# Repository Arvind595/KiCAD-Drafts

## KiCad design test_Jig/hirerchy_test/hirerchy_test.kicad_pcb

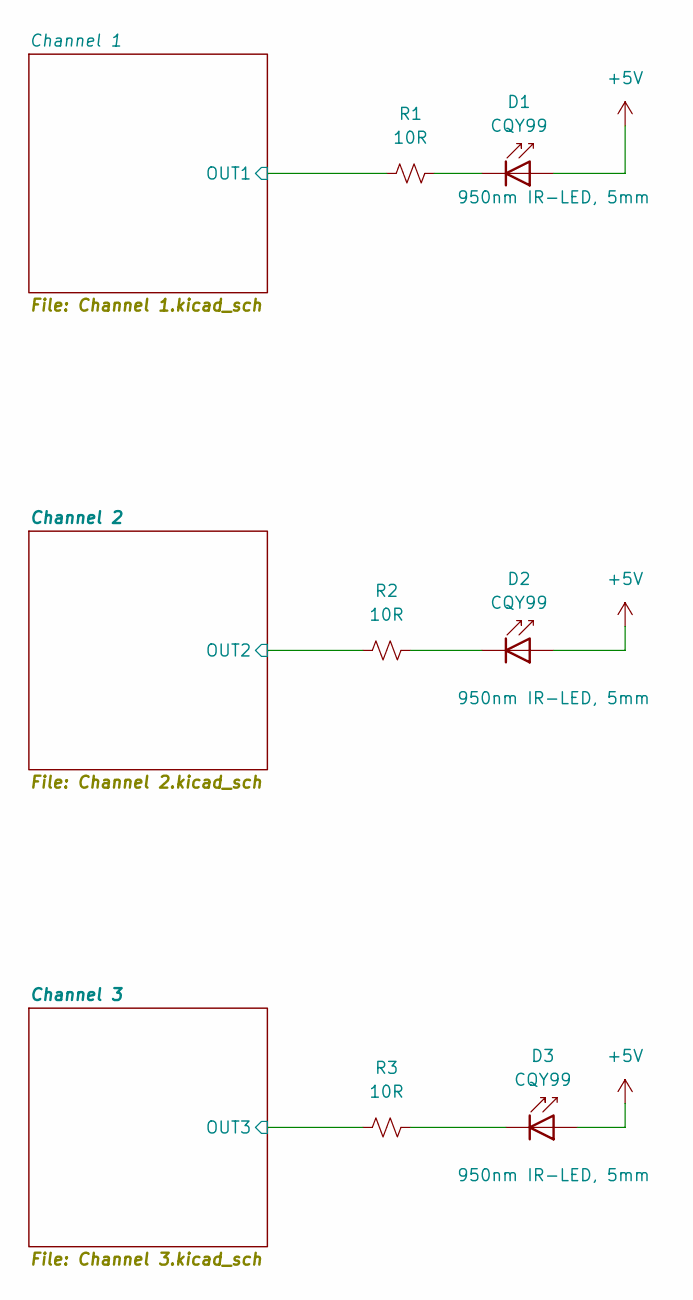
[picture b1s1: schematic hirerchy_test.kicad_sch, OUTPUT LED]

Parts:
D1, D2, D3: CQY99; LED_D5.0mm_IRGrey
R1, R2, R3: 10R; R_0805_2012Metric

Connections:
+5V: D1.2 (A), D2.2 (A), D3.2 (A); also elsewhere on the board
/Channel 1/OUT1: R1.1; also elsewhere on the board
/Channel 2/OUT2: R2.1; also elsewhere on the board
/Channel 3/OUT3: R3.1; also elsewhere on the board
unnamed: D1.1 (K), R1.2
unnamed: D2.1 (K), R2.2
unnamed: D3.1 (K), R3.2

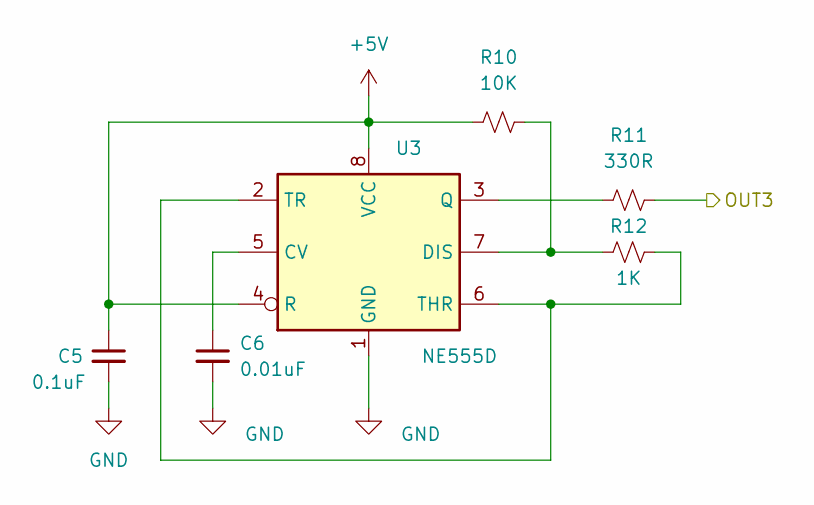
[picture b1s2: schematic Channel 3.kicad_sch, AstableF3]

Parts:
C5: 0.1uF; C_0805_2012Metric
C6: 0.01uF; C_0805_2012Metric
R10: 10K; R_0805_2012Metric
R11: 330R; R_0805_2012Metric
R12: 1K; R_0805_2012Metric
U3: NE555D; SOIC-8_3.9x4.9mm_P1.27mm

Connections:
+5V: C5.1, R10.1, U3.4 (R), U3.8 (VCC); also elsewhere on the board
/Channel 3/OUT3: R11.2; also elsewhere on the board
GND: C5.2, C6.2, U3.1 (GND); also elsewhere on the board
unnamed: C6.1, U3.5 (CV)
unnamed: R10.2, R12.1, U3.7 (DIS)
unnamed: R11.1, U3.3 (Q)
unnamed: R12.2, U3.2 (TR), U3.6 (THR)

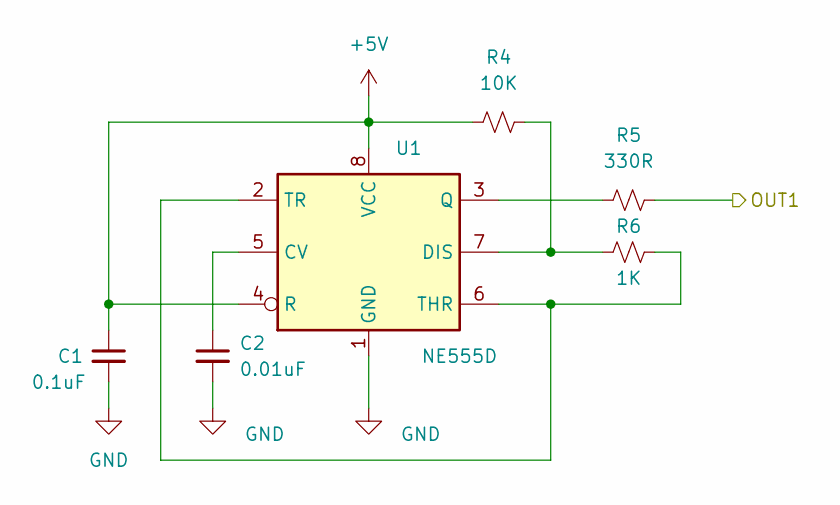
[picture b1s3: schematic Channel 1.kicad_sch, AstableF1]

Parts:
C1: 0.1uF; C_0805_2012Metric
C2: 0.01uF; C_0805_2012Metric
R4: 10K; R_0805_2012Metric
R5: 330R; R_0805_2012Metric
R6: 1K; R_0805_2012Metric
U1: NE555D; SOIC-8_3.9x4.9mm_P1.27mm

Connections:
+5V: C1.1, R4.1, U1.4 (R), U1.8 (VCC); also elsewhere on the board
/Channel 1/OUT1: R5.2; also elsewhere on the board
GND: C1.2, C2.2, U1.1 (GND); also elsewhere on the board
unnamed: C2.1, U1.5 (CV)
unnamed: R4.2, R6.1, U1.7 (DIS)
unnamed: R5.1, U1.3 (Q)
unnamed: R6.2, U1.2 (TR), U1.6 (THR)

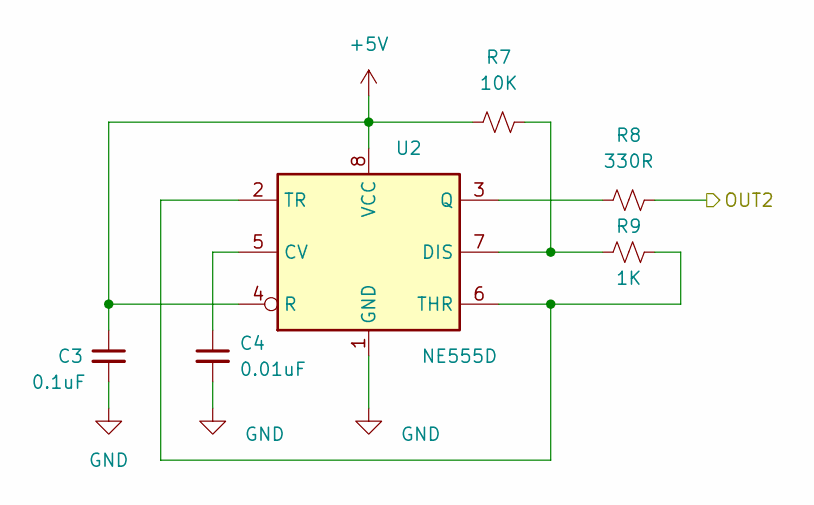
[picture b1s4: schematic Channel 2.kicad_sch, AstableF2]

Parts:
C3: 0.1uF; C_0805_2012Metric
C4: 0.01uF; C_0805_2012Metric
R7: 10K; R_0805_2012Metric
R8: 330R; R_0805_2012Metric
R9: 1K; R_0805_2012Metric
U2: NE555D; SOIC-8_3.9x4.9mm_P1.27mm

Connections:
+5V: C3.1, R7.1, U2.4 (R), U2.8 (VCC); also elsewhere on the board
/Channel 2/OUT2: R8.2; also elsewhere on the board
GND: C3.2, C4.2, U2.1 (GND); also elsewhere on the board
unnamed: C4.1, U2.5 (CV)
unnamed: R7.2, R9.1, U2.7 (DIS)
unnamed: R8.1, U2.3 (Q)
unnamed: R9.2, U2.2 (TR), U2.6 (THR)

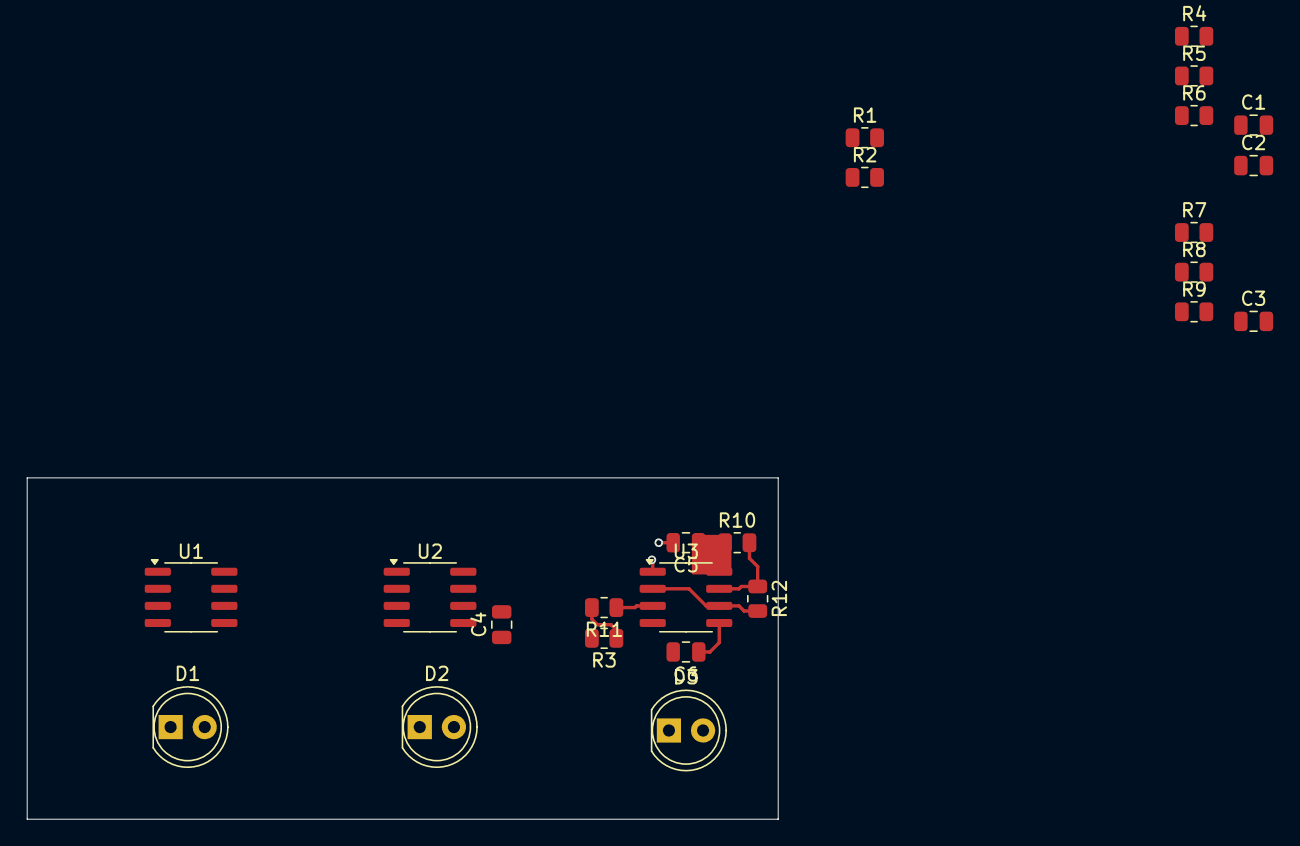
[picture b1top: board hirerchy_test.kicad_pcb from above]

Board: 4 copper layers, 55.9 x 25.4 mm, 24 parts (0 on the bottom side), 20 nets.

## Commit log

2024-10-24 initial
    not final
2024-10-24 another one
    not final too
